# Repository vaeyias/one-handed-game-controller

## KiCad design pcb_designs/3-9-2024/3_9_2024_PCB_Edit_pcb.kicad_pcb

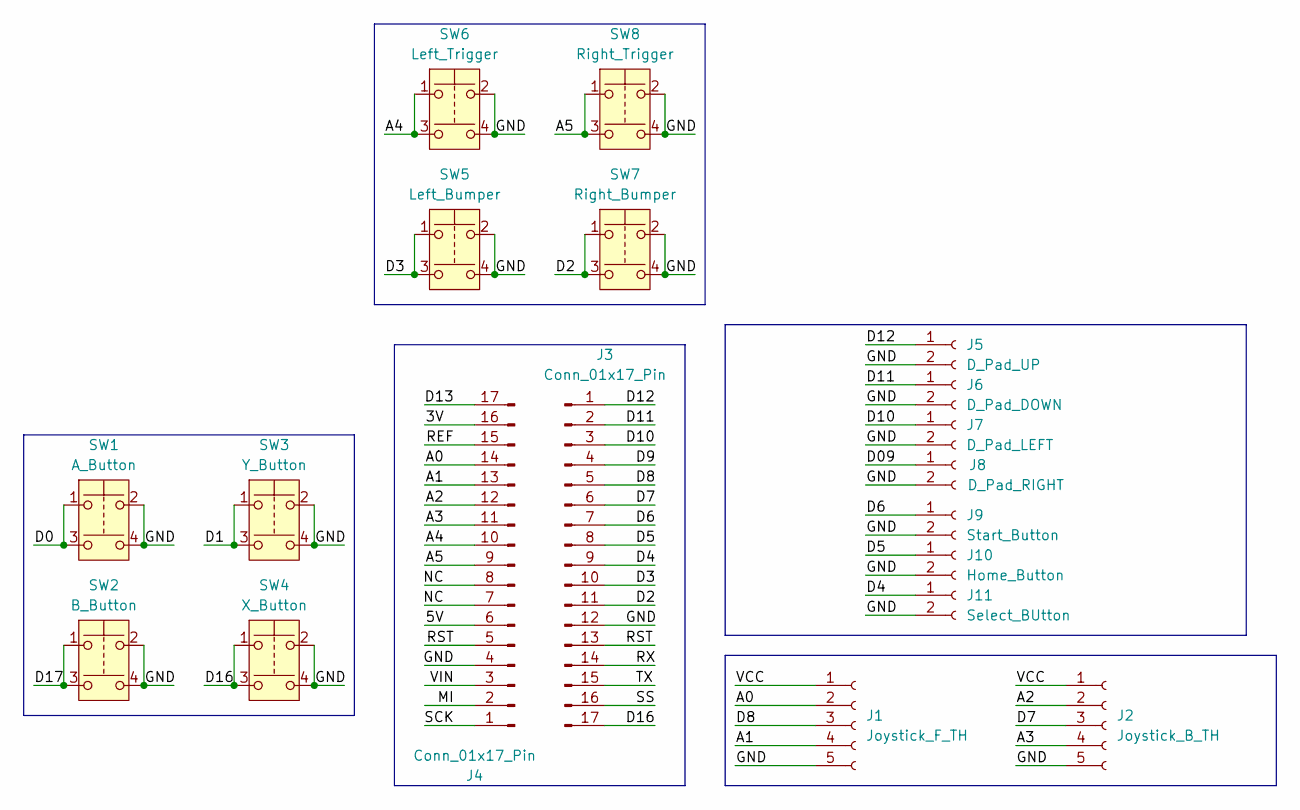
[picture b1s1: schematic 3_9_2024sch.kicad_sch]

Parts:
J1: Joystick_F_TH; SolderWire-0.1sqmm_1x05_P3.6mm_D0.4mm_OD1mm
J2: Joystick_B_TH; SolderWire-0.1sqmm_1x05_P3.6mm_D0.4mm_OD1mm
J3, J4: Conn_01x17_Pin; PinSocket_1x17_P2.54mm_Vertical
J5: D_Pad_UP; SolderWire-0.1sqmm_1x02_P3.6mm_D0.4mm_OD1mm
J6: D_Pad_DOWN; SolderWire-0.1sqmm_1x02_P3.6mm_D0.4mm_OD1mm
J7: D_Pad_LEFT; SolderWire-0.1sqmm_1x02_P3.6mm_D0.4mm_OD1mm
J8: D_Pad_RIGHT; SolderWire-0.1sqmm_1x02_P3.6mm_D0.4mm_OD1mm
J9: Start_Button; SolderWire-0.1sqmm_1x02_P3.6mm_D0.4mm_OD1mm
J10: Home_Button; SolderWire-0.1sqmm_1x02_P3.6mm_D0.4mm_OD1mm
J11: Select_BUtton; SolderWire-0.1sqmm_1x02_P3.6mm_D0.4mm_OD1mm
SW1: A_Button; D6R90_CNK
SW2: B_Button; D6R90_CNK
SW3: Y_Button; D6R90_CNK
SW4: X_Button; D6R90_CNK
SW5: Left_Bumper; D6R90_CNK
SW6: Left_Trigger; D6R90_CNK
SW7: Right_Bumper; D6R90_CNK
SW8: Right_Trigger; D6R90_CNK

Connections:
/3V: J4.16
/5V: J4.6
/A0: J1.2, J4.14
/A1: J1.4, J4.13
/A2: J2.2, J4.12
/A3: J2.4, J4.11
/A4: J4.10, SW6.1, SW6.3
/A5: J4.9, SW8.1, SW8.3
/D0: SW1.1, SW1.3
/D1: SW3.1, SW3.3
/D2: J3.11, SW7.1, SW7.3
/D3: J3.10, SW5.1, SW5.3
/D4: J3.9, J11.1
/D5: J3.8, J10.1
/D6: J3.7, J9.1
/D7: J2.3, J3.6
/D8: J1.3, J3.5
/D9: J3.4
/D09: J8.1
/D10: J3.3, J7.1
/D11: J3.2, J6.1
/D12: J3.1, J5.1
/D13: J4.17
/D16: J3.17, SW4.1, SW4.3
/D17: SW2.1, SW2.3
/GND: J1.5, J2.5, J3.12, J4.4, J5.2, J6.2, J7.2, J8.2, J9.2, J10.2, J11.2, SW1.2, SW1.4, SW2.2, SW2.4, SW3.2, SW3.4, SW4.2, SW4.4, SW5.2, SW5.4, SW6.2, SW6.4, SW7.2, SW7.4, SW8.2, SW8.4
/MI: J4.2
/NC: J4.7, J4.8
/REF: J4.15
/RST: J3.13, J4.5
/RX: J3.14
/SCK: J4.1
/SS: J3.16
/TX: J3.15
/VCC: J1.1, J2.1
/VIN: J4.3

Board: 2 copper layers, 19 parts (0 on the bottom side), 24 nets, no tracks yet.
